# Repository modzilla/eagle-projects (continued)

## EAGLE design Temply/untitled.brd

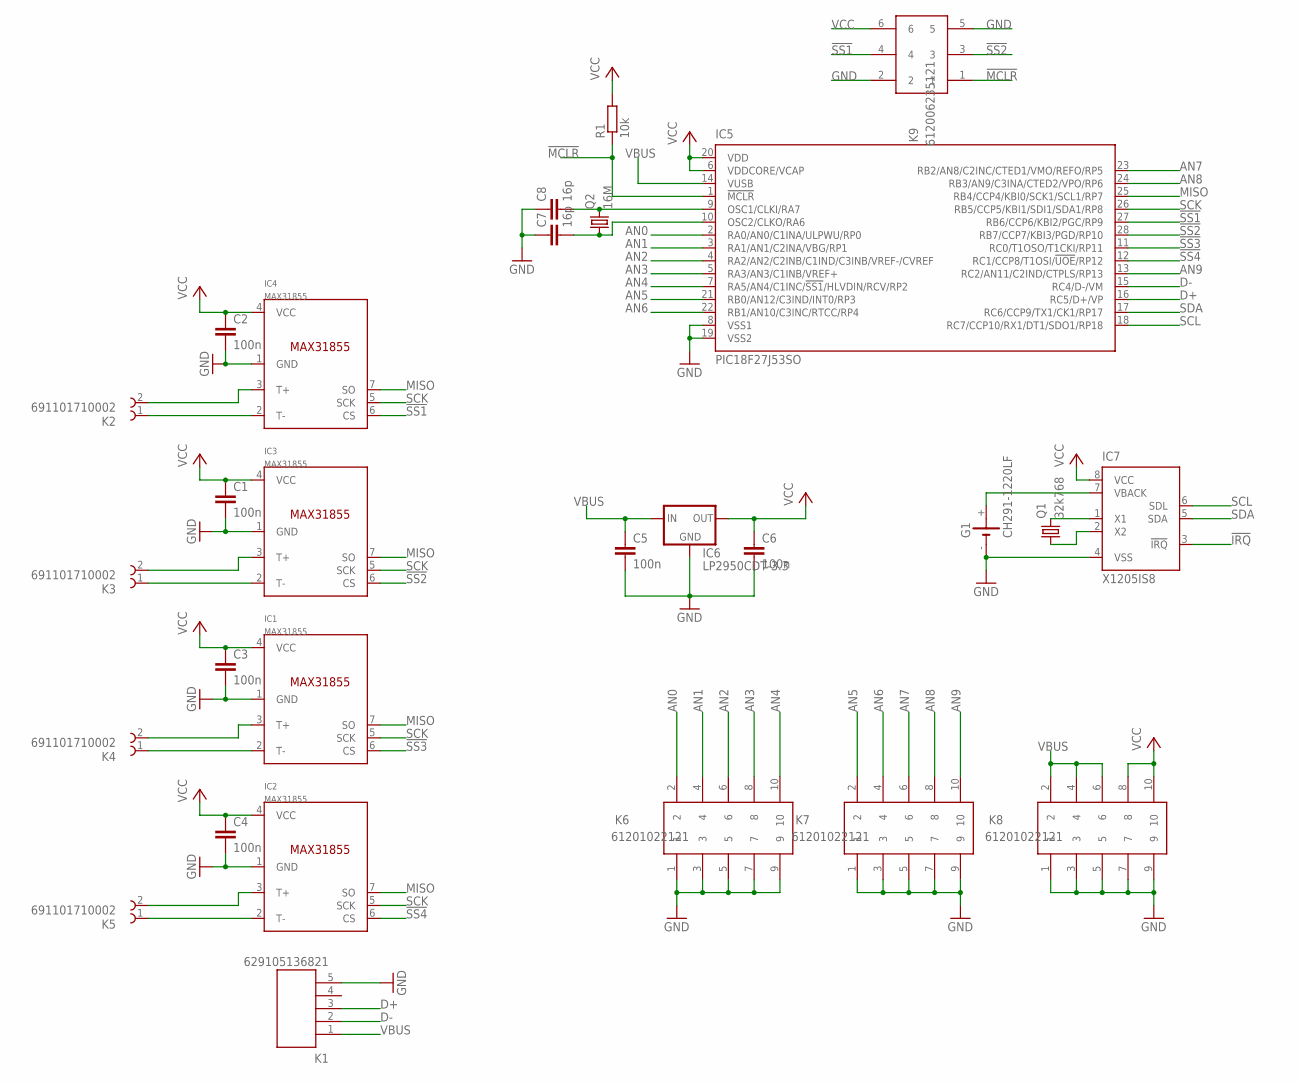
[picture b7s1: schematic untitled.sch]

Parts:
C1, C2, C3, C4, C5, C6: 100n; C1206
C7, C8: 16p; C0805
G1: CH291-1220LF
IC1, IC2, IC3, IC4: MAX31855; SOIC8
IC5: PIC18F27J53SO; SO28W
IC6: LP2950CDT-3.3; DPACK
IC7: X1205IS8; SO-08
K1: 629105136821
K2, K3, K4, K5: 691101710002
K6, K7, K8: 61201022121
K9: 612006235121
Q1: 32k768; TC26H
Q2: 16M; CTS406
R1: 10k; M1206

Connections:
!IRQ: IC7.3 (!IRQ)
!MCLR: IC5.1 (!MCLR), K9.1, R1.1
!SS1: IC4.6 (CS), IC5.27 (RB6/CCP6/KBI2/PGC/RP9), K9.4
!SS2: IC3.6 (CS), IC5.28 (RB7/CCP7/KBI3/PGD/RP10), K9.3
!SS3: IC1.6 (CS), IC5.11 (RC0/T1OSO/T1CKI/RP11)
!SS4: IC2.6 (CS), IC5.12 (RC1/CCP8/T1OSI/!UOE!/RP12)
AN0: IC5.2 (RA0/AN0/C1INA/ULPWU/RP0), K6.2
AN1: IC5.3 (RA1/AN1/C2INA/VBG/RP1), K6.4
AN2: IC5.4 (RA2/AN2/C2INB/C1IND/C3INB/VREF-/CVREF), K6.6
AN3: IC5.5 (RA3/AN3/C1INB/VREF+), K6.8
AN4: IC5.7 (RA5/AN4/C1INC/!SS1!/HLVDIN/RCV/RP2), K6.10
AN5: IC5.21 (RB0/AN12/C3IND/INT0/RP3), K7.2
AN6: IC5.22 (RB1/AN10/C3INC/RTCC/RP4), K7.4
AN7: IC5.23 (RB2/AN8/C2INC/CTED1/VMO/REFO/RP5), K7.6
AN8: IC5.24 (RB3/AN9/C3INA/CTED2/VPO/RP6), K7.8
AN9: IC5.13 (RC2/AN11/C2IND/CTPLS/RP13), K7.10
D+: IC5.16 (RC5/D+/VP), K1.3
D-: IC5.15 (RC4/D-/VM), K1.2
GND: C1.2, C2.2, C3.2, C4.2, C5.2, C6.2, C7.1, C8.1, G1.-, IC1.1 (GND), IC2.1 (GND), IC3.1 (GND), IC4.1 (GND), IC5.8 (VSS1), IC5.19 (VSS2), IC6.4 (GND), IC7.4 (VSS), K1.5, K6.1, K6.3, K6.5, K6.7, K6.9, K7.1, K7.3, K7.5, K7.7, K7.9, K8.1, K8.3, K8.5, K8.7, K8.9, K9.2, K9.5
MISO: IC1.7 (SO), IC2.7 (SO), IC3.7 (SO), IC4.7 (SO), IC5.25 (RB4/CCP4/KBI0/SCK1/SCL1/RP7)
unnamed: IC4.2 (T-), K2.1
unnamed: IC4.3 (T+), K2.2
unnamed: IC3.3 (T+), K3.2
unnamed: IC3.2 (T-), K3.1
unnamed: IC1.3 (T+), K4.2
unnamed: IC1.2 (T-), K4.1
unnamed: IC2.3 (T+), K5.2
unnamed: IC2.2 (T-), K5.1
unnamed: IC7.1 (X1), Q1.2
unnamed: IC7.2 (X2), Q1.1
unnamed: C8.2, IC5.9 (OSC1/CLKI/RA7), Q2.3 (2)
unnamed: G1.+, IC7.7 (VBACK)
unnamed: C7.2, IC5.10 (OSC2/CLKO/RA6), Q2.1
SCK: IC1.5 (SCK), IC2.5 (SCK), IC3.5 (SCK), IC4.5 (SCK), IC5.26 (RB5/CCP5/KBI1/SDI1/SDA1/RP8)
SCL: IC5.18 (RC7/CCP10/RX1/DT1/SDO1/RP18), IC7.6 (SDL)
SDA: IC5.17 (RC6/CCP9/TX1/CK1/RP17), IC7.5 (SDA)
VBUS: C5.1, IC5.14 (VUSB), IC6.1 (IN), K1.1, K8.2, K8.4, K8.6
VCC: C1.1, C2.1, C3.1, C4.1, C6.1, IC1.4 (VCC), IC2.4 (VCC), IC3.4 (VCC), IC4.4 (VCC), IC5.6 (VDDCORE/VCAP), IC5.20 (VDD), IC6.3 (OUT), IC7.8 (VCC), K8.8, K8.10, K9.6, R1.2

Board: 4 copper layers, 28 parts (0 on the bottom side), 37 nets, no tracks yet.

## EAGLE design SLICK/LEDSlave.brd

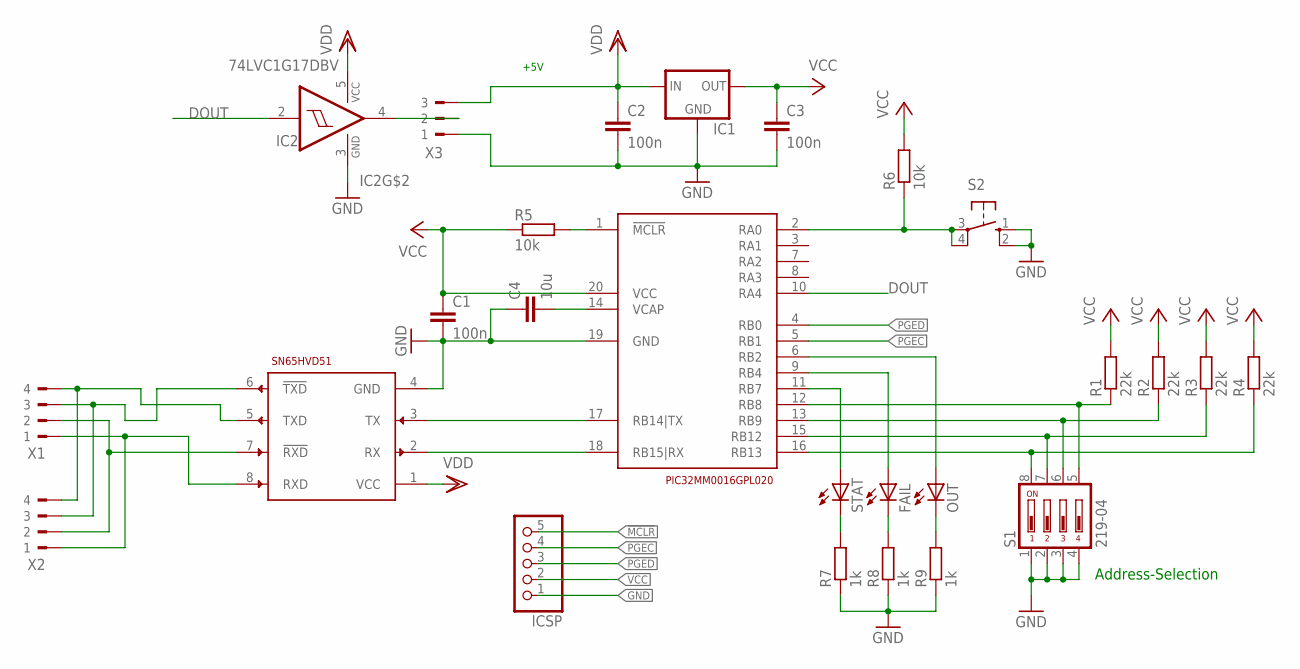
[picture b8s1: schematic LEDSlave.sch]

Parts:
C1, C2, C3: 100n; C0805
C4: 10u; C1206
FAIL: LED3MM
IC1: LP2950CZ-3.3; TO92
IC2: 74LVC1G17DBV; SOT23-5
ICSP: PINHD-1X5; 1X05
OUT: LED3MM
R1, R2, R3, R4: 22k; R0805
R5, R6: 10k; R0805
R7, R8, R9: 1k; R0805
S1: 219-04; CTS-219-04
S2: 10-XX; B3F-10XX
STAT: LED3MM
U$1: PIC32MM0016GPL020; SSOP20
U$2: SN65HVD51; SO-08
X1, X2: 90-4
X3: 90-3

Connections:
!MCLR: ICSP.5, R5.2, U$1.1 (!MCLR)
DOUT: IC2.2 (I), U$1.10 (RA4)
GND: C1.2, C2.2, C3.2, C4.1, IC1.2 (GND), IC2.3 (GND), ICSP.1, R7.1, R8.1, R9.1, S1.1, S1.2, S1.3, S1.4, S2.1 (S), S2.2 (S1), U$1.19 (GND), U$2.4 (GND), X3.1
unnamed: U$1.17 (RB14|TX), U$2.3 (TX)
unnamed: U$1.18 (RB15|RX), U$2.2 (RX)
unnamed: R4.1, S1.8, U$1.16 (RB13)
unnamed: R3.1, S1.7, U$1.15 (RB12)
unnamed: R2.1, S1.6, U$1.13 (RB9)
unnamed: R1.1, S1.5, U$1.12 (RB8)
unnamed: STAT.A, U$1.11 (RB7)
unnamed: IC2.4 (O), X3.2
unnamed: R6.1, S2.3, S2.4 (P1), U$1.2 (RA0)
unnamed: FAIL.A, U$1.9 (RB4)
unnamed: C4.2, U$1.14 (VCAP)
unnamed: U$2.7 (!RXD), X1.2, X2.2
unnamed: U$2.6 (!TXD), X1.3, X2.3
unnamed: OUT.A, U$1.6 (RB2)
unnamed: R7.2, STAT.K (C)
unnamed: FAIL.K (C), R8.2
unnamed: OUT.K (C), R9.2
unnamed: U$2.8 (RXD), X1.1, X2.1
unnamed: U$2.5 (TXD), X1.4, X2.4
PGEC: ICSP.4, U$1.5 (RB1)
PGED: ICSP.3, U$1.4 (RB0)
VCC: C1.1, C3.1, IC1.1 (OUT), ICSP.2, R1.2, R2.2, R3.2, R4.2, R5.1, R6.2, U$1.20 (VCC)
VDD: C2.1, IC1.3 (IN), IC2.5 (VCC), U$2.1 (VCC), X3.3

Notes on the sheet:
Address-Selection
+5V

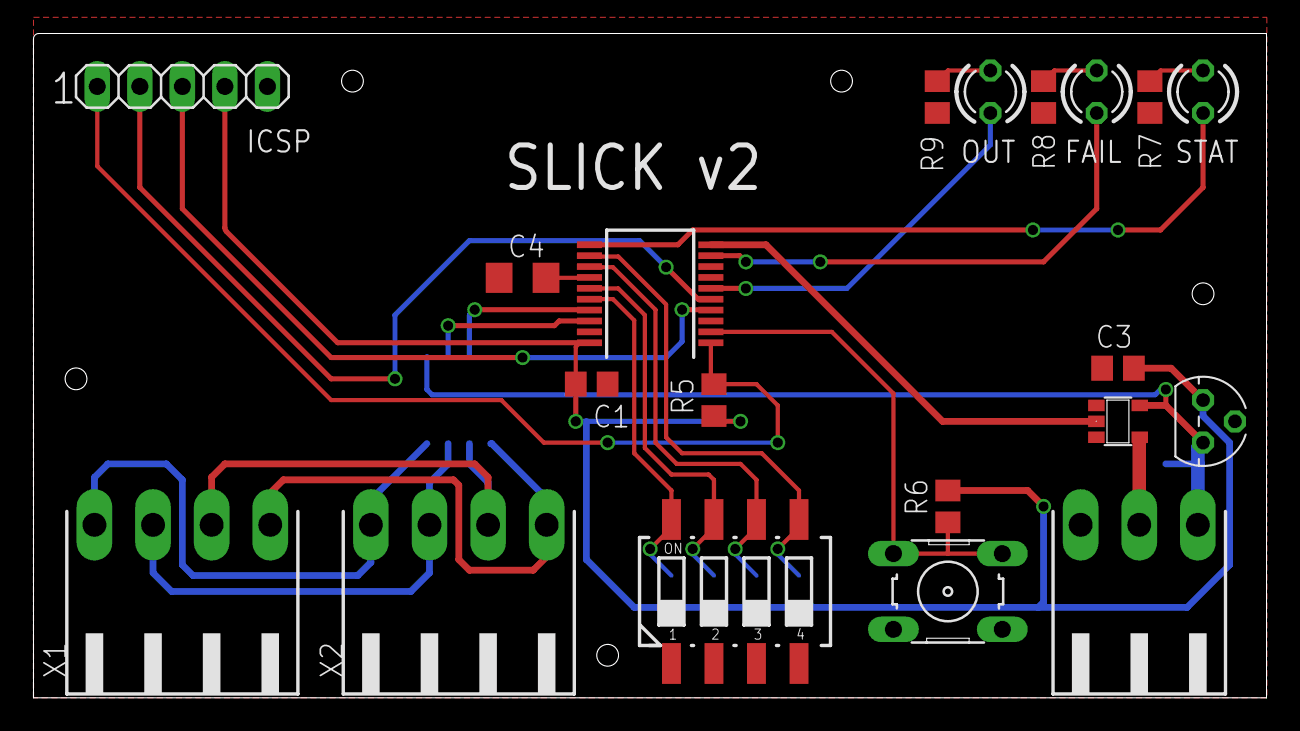
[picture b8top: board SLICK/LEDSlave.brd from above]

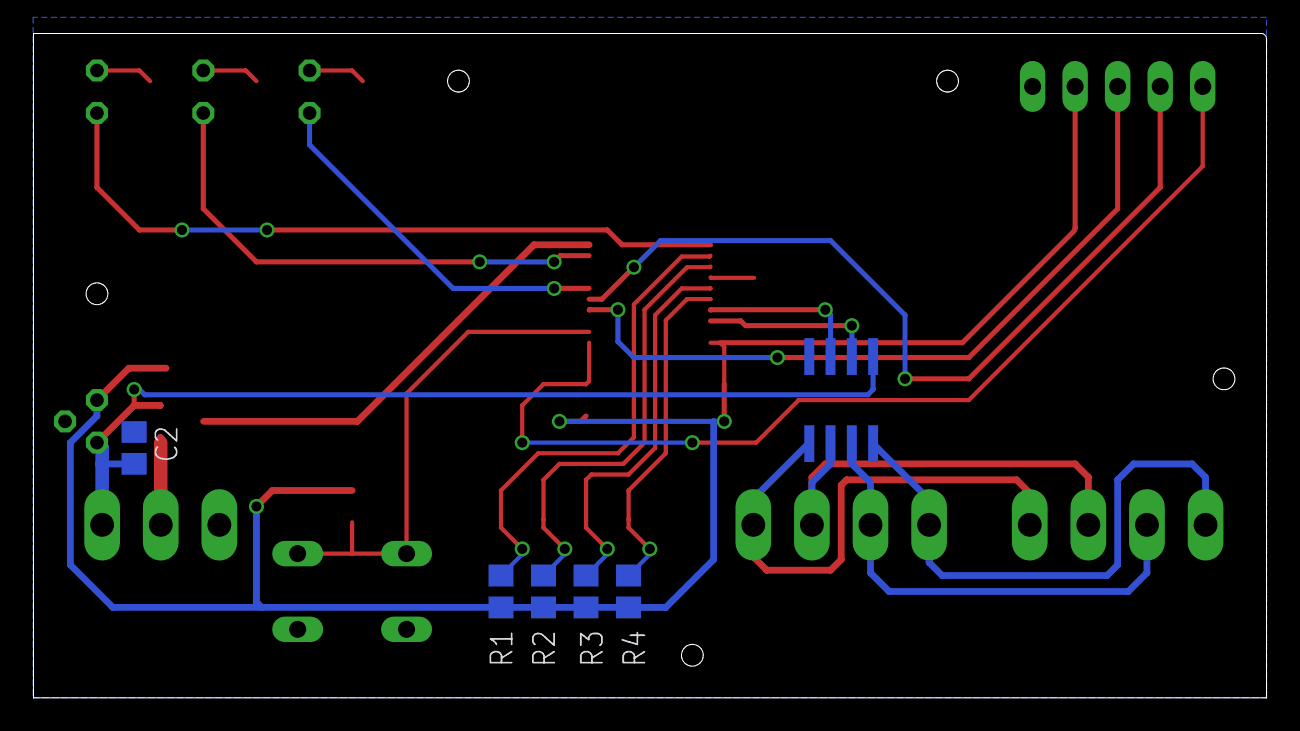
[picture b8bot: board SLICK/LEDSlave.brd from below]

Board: 2 copper layers, 73.6 x 39.7 mm, 26 parts (6 on the bottom side), 26 nets.

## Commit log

2017-03-27 First real commit
2017-03-27 removed empty/unneeded projects
2017-03-27 added readme
2017-03-27 fix readme cos noob
2017-04-04 some changes
